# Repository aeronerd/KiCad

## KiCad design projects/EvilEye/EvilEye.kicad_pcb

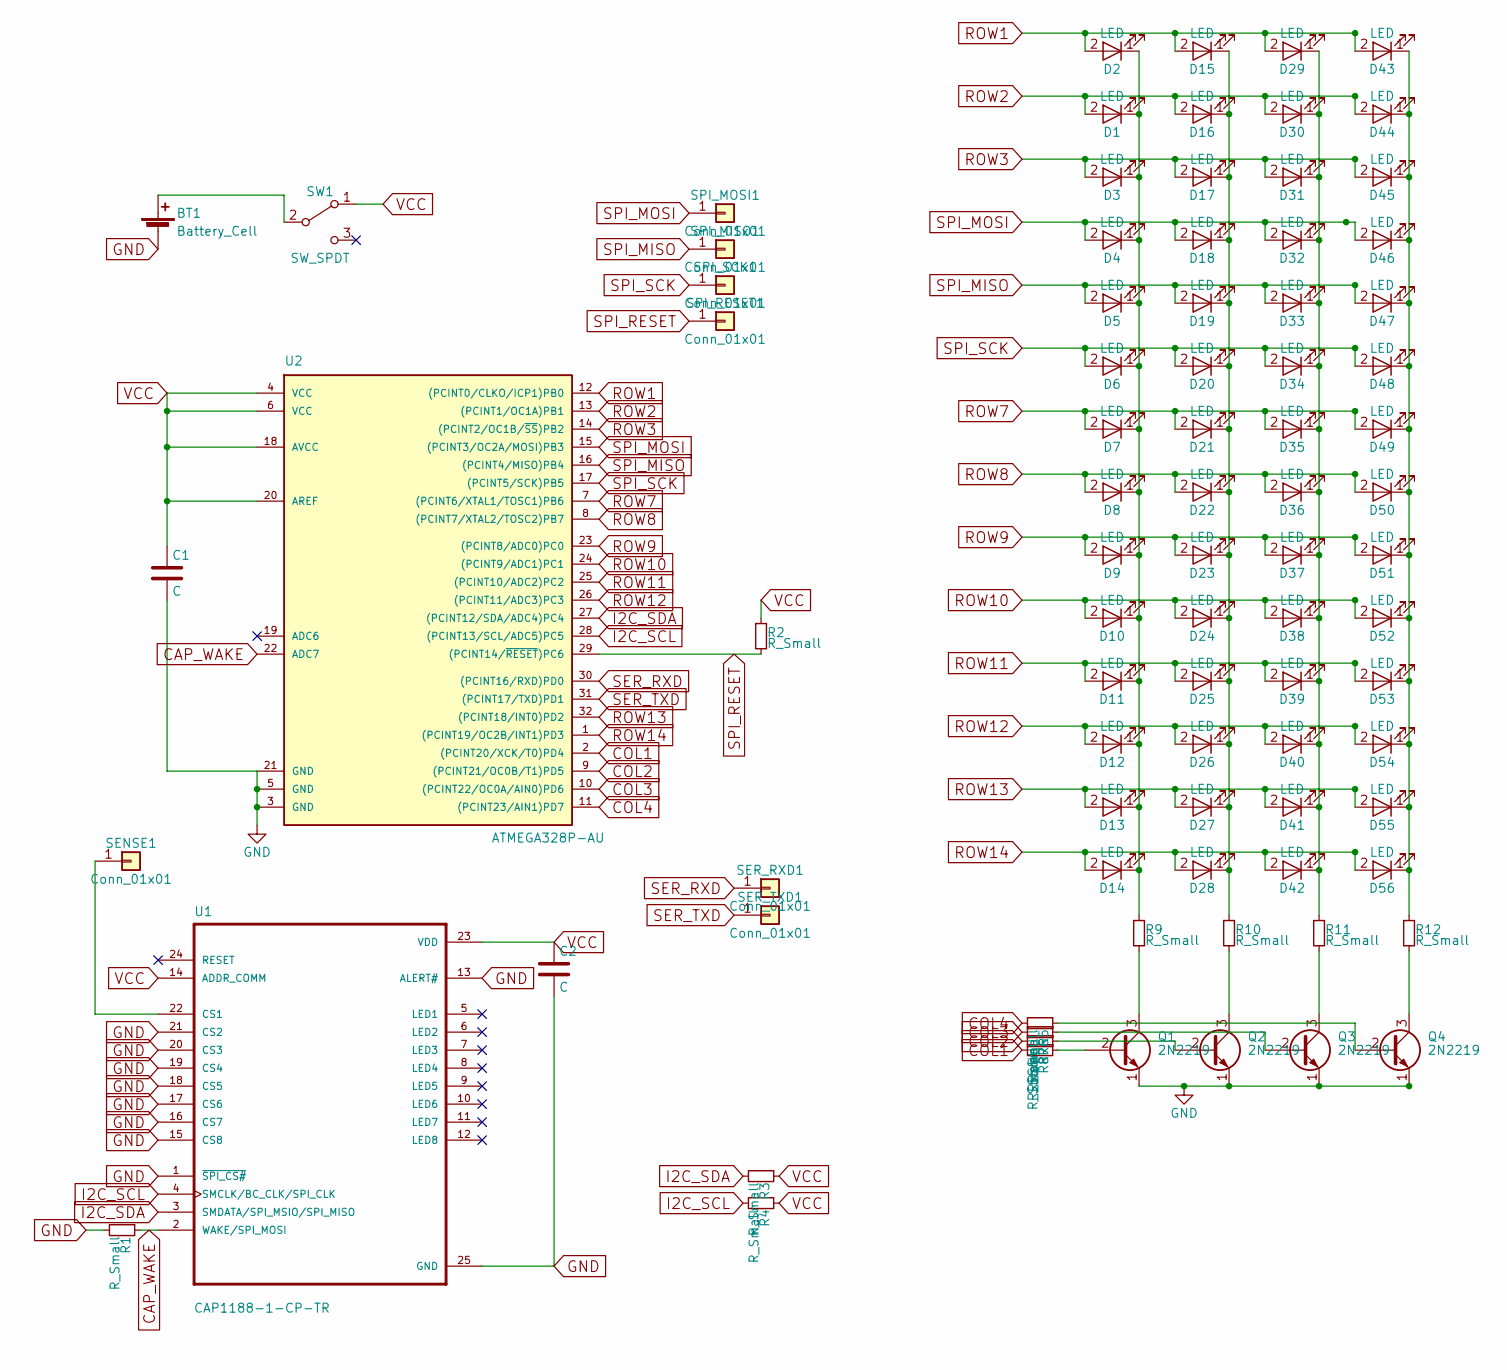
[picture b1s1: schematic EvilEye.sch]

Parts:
BT1: Battery_Cell; 2032-CoinCell-top-bottom
C1, C2: C; C_0603
D1, D2, D3, D4, D5, D6, D7, D8, D9, D10, D11, D12, D13, D14, D15, D16, D17, D18, D19, D20, D21, D22, D23, D24, D25, D26, D27, D28, D29, D30, D31, D32, D33, D34, D35, D36, D37, D38, D39, D40, D41, D42, D43, D44, D45, D46, D47, D48, D49, D50, D51, D52, D53, D54, D55, D56: LED; LED_1206
Q1, Q2, Q3, Q4: 2N2219; SOT23
R1, R2, R3, R4, R5, R6, R7, R8, R9, R10, R11, R12: R_Small; R_0603
SENSE1: Conn_01x01; Measurement_Point_Square-SMD-Pad_Small
SER_RXD1: Conn_01x01; Measurement_Point_Square-SMD-Pad_Small
SER_TXD1: Conn_01x01; Measurement_Point_Square-SMD-Pad_Small
SPI_MISO1: Conn_01x01; Measurement_Point_Square-SMD-Pad_Small
SPI_MOSI1: Conn_01x01; Measurement_Point_Square-SMD-Pad_Small
SPI_RESET1: Conn_01x01; Measurement_Point_Square-SMD-Pad_Small
SPI_SCK1: Conn_01x01; Measurement_Point_Square-SMD-Pad_Small
SW1: SW_SPDT; SW_SPDT_SMD
U1: CAP1188-1-CP-TR; QFN50P400X400X90-25N
U2: ATMEGA328P-AU; TQFP-32_7x7mm_Pitch0.8mm

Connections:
CAP_WAKE: R1.1, U1.2 (WAKE/SPI_MOSI), U2.22 (ADC7)
COL1: R8.2, U2.2 ((PCINT20/XCK/T0)PD4)
COL2: R7.2, U2.9 ((PCINT21/OC0B/T1)PD5)
COL3: R6.2, U2.10 ((PCINT22/OC0A/AIN0)PD6)
COL4: R5.2, U2.11 ((PCINT23/AIN1)PD7)
GND: BT1.2 (-), C1.2, C2.2, Q1.1 (E), Q2.1 (E), Q3.1 (E), Q4.1 (E), R1.2, U1.1 (~SPI_CS#~), U1.13 (ALERT#), U1.15 (CS8), U1.16 (CS7), U1.17 (CS6), U1.18 (CS5), U1.19 (CS4), U1.20 (CS3), U1.21 (CS2), U1.25 (GND), U2.3 (GND), U2.5 (GND), U2.21 (GND)
I2C_SCL: R4.2, U1.4 (SMCLK/BC_CLK/SPI_CLK), U2.28 ((PCINT13/SCL/ADC5)PC5)
I2C_SDA: R3.2, U1.3 (SMDATA/SPI_MSIO/SPI_MISO), U2.27 ((PCINT12/SDA/ADC4)PC4)
unnamed: BT1.1 (+), SW1.2 (B)
unnamed: D1.1 (K), D2.1 (K), D3.1 (K), D4.1 (K), D5.1 (K), D6.1 (K), D7.1 (K), D8.1 (K), D9.1 (K), D10.1 (K), D11.1 (K), D12.1 (K), D13.1 (K), D14.1 (K), R9.1
unnamed: D15.1 (K), D16.1 (K), D17.1 (K), D18.1 (K), D19.1 (K), D20.1 (K), D21.1 (K), D22.1 (K), D23.1 (K), D24.1 (K), D25.1 (K), D26.1 (K), D27.1 (K), D28.1 (K), R10.1
unnamed: D29.1 (K), D30.1 (K), D31.1 (K), D32.1 (K), D33.1 (K), D34.1 (K), D35.1 (K), D36.1 (K), D37.1 (K), D38.1 (K), D39.1 (K), D40.1 (K), D41.1 (K), D42.1 (K), R11.1
unnamed: D43.1 (K), D44.1 (K), D45.1 (K), D46.1 (K), D47.1 (K), D48.1 (K), D49.1 (K), D50.1 (K), D51.1 (K), D52.1 (K), D53.1 (K), D54.1 (K), D55.1 (K), D56.1 (K), R12.1
unnamed: Q1.2 (B), R8.1
unnamed: Q1.3 (C), R9.2
unnamed: Q2.2 (B), R7.1
unnamed: Q2.3 (C), R10.2
unnamed: Q3.2 (B), R6.1
unnamed: Q3.3 (C), R11.2
unnamed: Q4.2 (B), R5.1
unnamed: Q4.3 (C), R12.2
unnamed: SENSE1.1, U1.22 (CS1)
ROW1: D2.2 (A), D15.2 (A), D29.2 (A), D43.2 (A), U2.12 ((PCINT0/CLKO/ICP1)PB0)
ROW2: D1.2 (A), D16.2 (A), D30.2 (A), D44.2 (A), U2.13 ((PCINT1/OC1A)PB1)
ROW3: D3.2 (A), D17.2 (A), D31.2 (A), D45.2 (A), U2.14 ((PCINT2/OC1B/~SS~)PB2)
ROW7: D7.2 (A), D21.2 (A), D35.2 (A), D49.2 (A), U2.7 ((PCINT6/XTAL1/TOSC1)PB6)
ROW8: D8.2 (A), D22.2 (A), D36.2 (A), D50.2 (A), U2.8 ((PCINT7/XTAL2/TOSC2)PB7)
ROW9: D9.2 (A), D23.2 (A), D37.2 (A), D51.2 (A), U2.23 ((PCINT8/ADC0)PC0)
ROW10: D10.2 (A), D24.2 (A), D38.2 (A), D52.2 (A), U2.24 ((PCINT9/ADC1)PC1)
ROW11: D11.2 (A), D25.2 (A), D39.2 (A), D53.2 (A), U2.25 ((PCINT10/ADC2)PC2)
ROW12: D12.2 (A), D26.2 (A), D40.2 (A), D54.2 (A), U2.26 ((PCINT11/ADC3)PC3)
ROW13: D13.2 (A), D27.2 (A), D41.2 (A), D55.2 (A), U2.32 ((PCINT18/INT0)PD2)
ROW14: D14.2 (A), D28.2 (A), D42.2 (A), D56.2 (A), U2.1 ((PCINT19/OC2B/INT1)PD3)
SER_RXD: SER_RXD1.1, U2.30 ((PCINT16/RXD)PD0)
SER_TXD: SER_TXD1.1, U2.31 ((PCINT17/TXD)PD1)
SPI_MISO: D5.2 (A), D19.2 (A), D33.2 (A), D47.2 (A), SPI_MISO1.1, U2.16 ((PCINT4/MISO)PB4)
SPI_MOSI: D4.2 (A), D18.2 (A), D32.2 (A), D46.2 (A), SPI_MOSI1.1, U2.15 ((PCINT3/OC2A/MOSI)PB3)
SPI_RESET: R2.2, SPI_RESET1.1, U2.29 ((PCINT14/~RESET~)PC6)
SPI_SCK: D6.2 (A), D20.2 (A), D34.2 (A), D48.2 (A), SPI_SCK1.1, U2.17 ((PCINT5/SCK)PB5)
VCC: C1.1, C2.1, R2.1, R3.1, R4.1, SW1.1 (A), U1.14 (ADDR_COMM), U1.23 (VDD), U2.4 (VCC), U2.6 (VCC), U2.18 (AVCC), U2.20 (AREF)

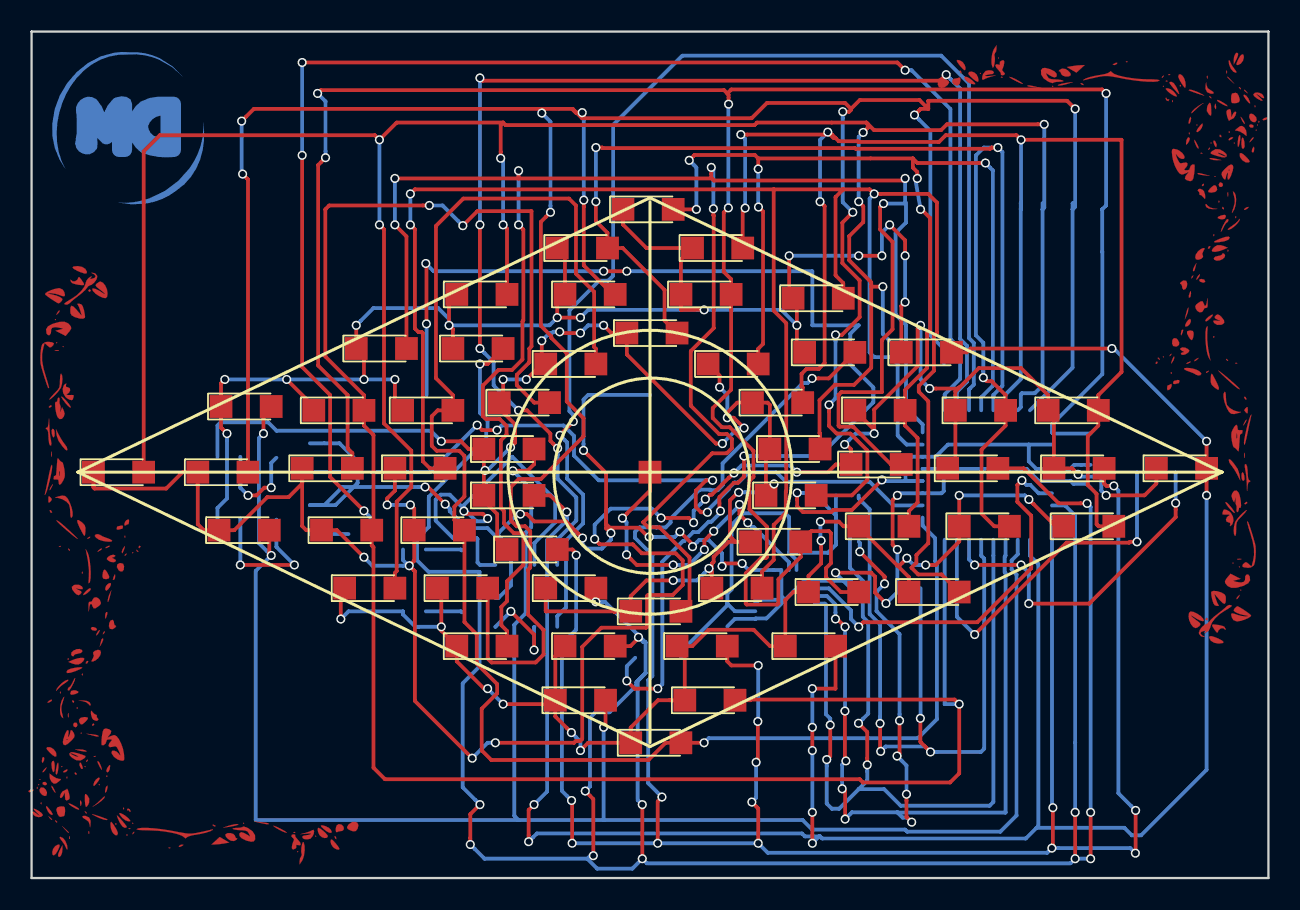
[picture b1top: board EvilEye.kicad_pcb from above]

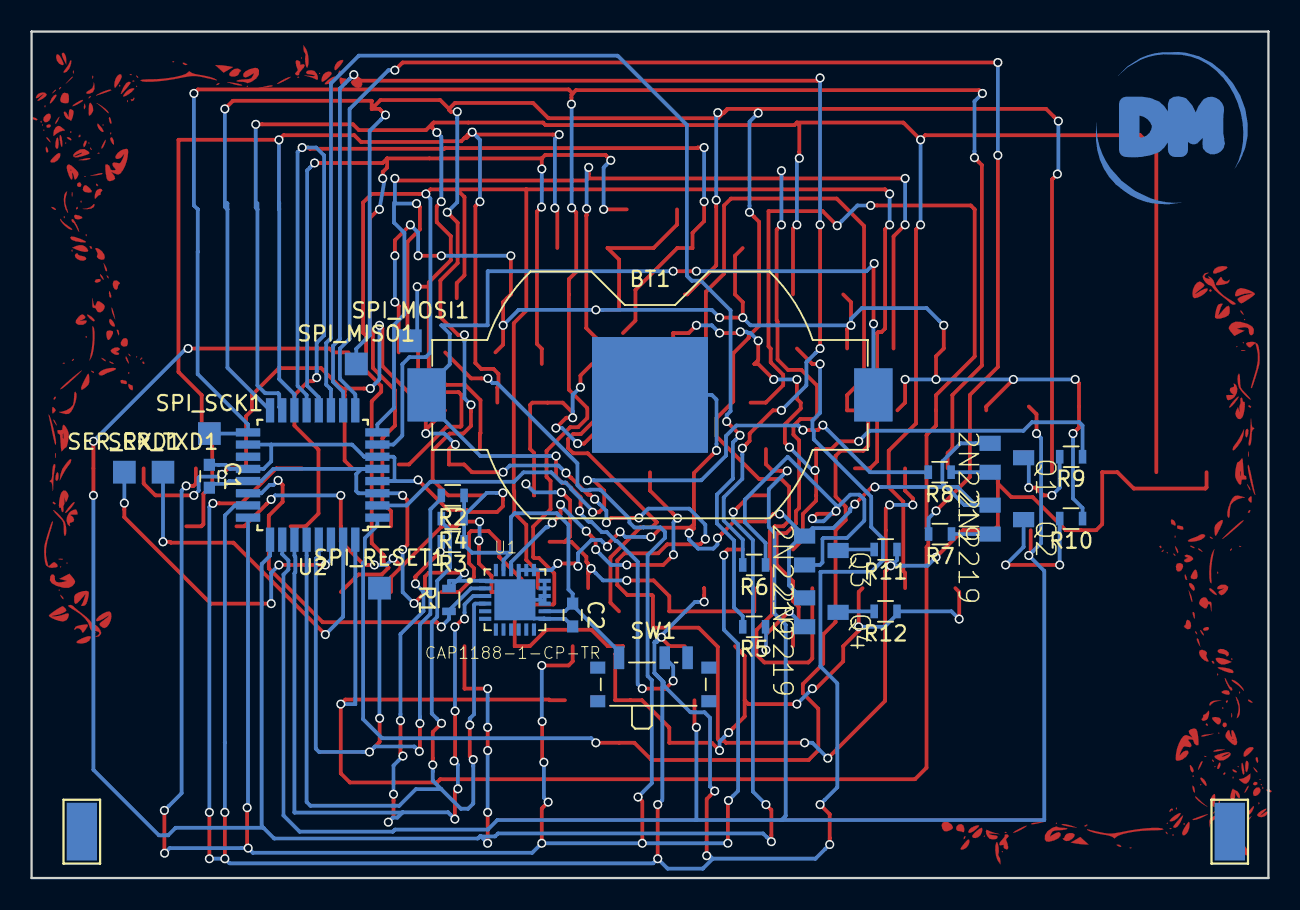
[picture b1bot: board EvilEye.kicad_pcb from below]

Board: 2 copper layers, 81.3 x 55.6 mm, 86 parts (29 on the bottom side), 40 nets.

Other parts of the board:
svg2mod: G***; logo_dm_10x10mm

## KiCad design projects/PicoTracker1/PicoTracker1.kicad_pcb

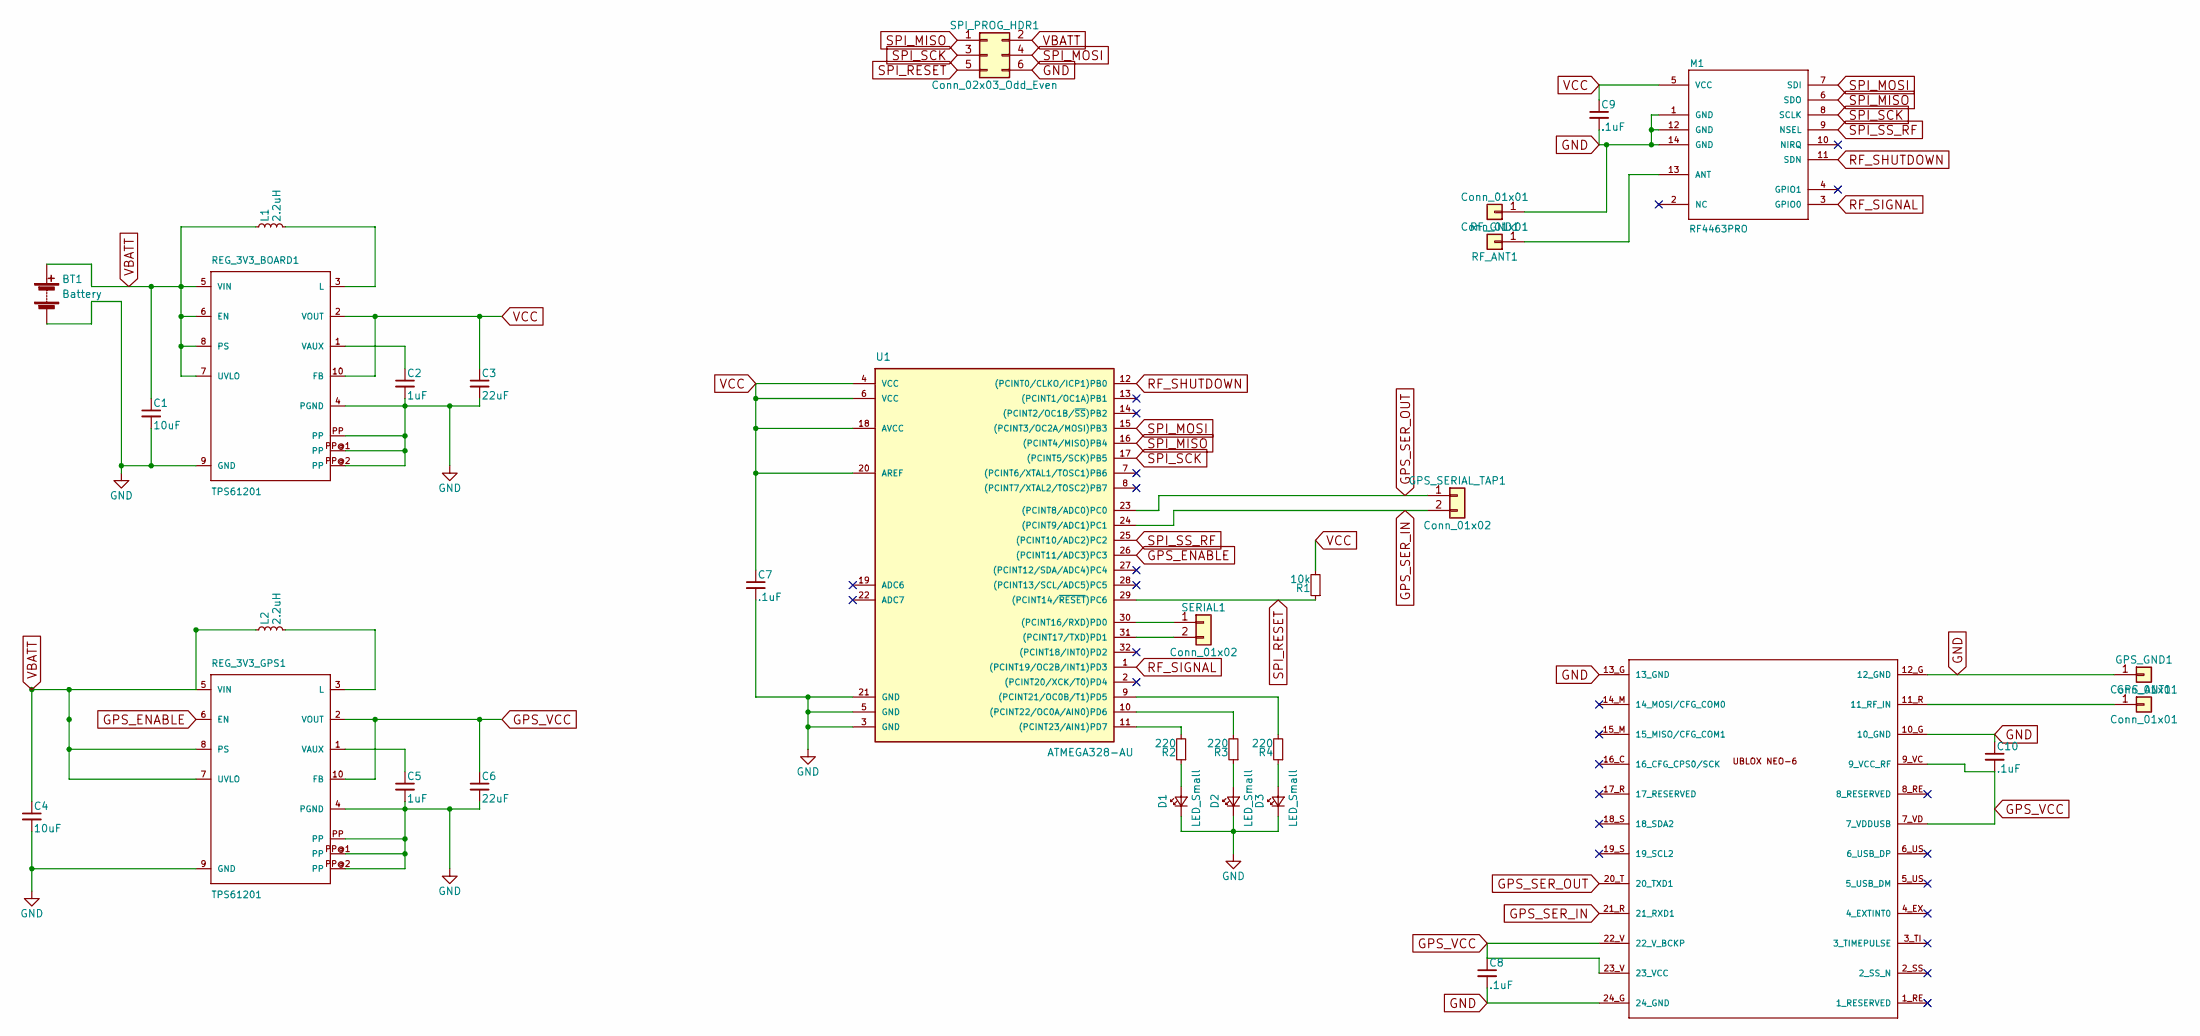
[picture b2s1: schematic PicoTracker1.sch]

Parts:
BT1: Battery; Pin_Header_Straight_1x02_Pitch2.54mm
C1, C4: 10uF; C_0603_HandSoldering
C2, C5: 1uF; C_0603_HandSoldering
C3, C6: 22uF; C_0603_HandSoldering
C7, C8, C9, C10: .1uF; C_0603_HandSoldering
D1, D2, D3: LED_Small; LED_0603_HandSoldering
GPS_ANT1: Conn_01x01; Measurement_Point_Square-SMD-Pad_Big
GPS_GND1: Conn_01x01; Measurement_Point_Square-SMD-Pad_Big
GPS_SERIAL_TAP1: Conn_01x02; Pin_Header_Straight_1x02_Pitch2.54mm
L1, L2: 2.2uH; L_0603_HandSoldering
M1: RF4463PRO; RF4436PRO-STD_BOARD
M2: UBLOX_NEO-6
R1: 10k; R_0603_HandSoldering
R2, R3, R4: 220; R_0603_HandSoldering
REG_3V3_BOARD1, REG_3V3_GPS1: TPS61201; texas-S-PDSO-N10
RF_ANT1: Conn_01x01; Measurement_Point_Square-SMD-Pad_Big
RF_GND1: Conn_01x01; Measurement_Point_Square-SMD-Pad_Big
SERIAL1: Conn_01x02; Pin_Header_Straight_1x02_Pitch2.54mm
SPI_PROG_HDR1: Conn_02x03_Odd_Even; Pin_Header_Straight_2x03_Pitch2.54mm
U1: ATMEGA328-AU; TQFP-32_7x7mm_Pitch0.8mm

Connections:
GND: BT1.2 (-), C1.2, C2.2, C3.2, C4.2, C5.2, C6.2, C7.2, C8.2, C9.2, C10.1, D1.1 (K), D2.1 (K), D3.1 (K), GPS_GND1.1, M1.1 (GND), M1.12 (GND), M1.14 (GND), M2.10_G (10_GND), M2.12_G (12_GND), M2.13_G (13_GND), M2.24_G (24_GND), REG_3V3_BOARD1.4 (PGND), REG_3V3_BOARD1.9 (GND), REG_3V3_BOARD1.PP, REG_3V3_BOARD1.PP@1 (PP), REG_3V3_BOARD1.PP@2 (PP), REG_3V3_GPS1.4 (PGND), REG_3V3_GPS1.9 (GND), REG_3V3_GPS1.PP, REG_3V3_GPS1.PP@1 (PP), REG_3V3_GPS1.PP@2 (PP), RF_GND1.1, SPI_PROG_HDR1.6, U1.3 (GND), U1.5 (GND), U1.21 (GND)
GPS_ENABLE: REG_3V3_GPS1.6 (EN), U1.26 ((PCINT11/ADC3)PC3)
GPS_SER_IN: GPS_SERIAL_TAP1.2, M2.21_R (21_RXD1), U1.24 ((PCINT9/ADC1)PC1)
GPS_SER_OUT: GPS_SERIAL_TAP1.1, M2.20_T (20_TXD1), U1.23 ((PCINT8/ADC0)PC0)
GPS_VCC: C6.1, C8.1, C10.2, M2.7_VD (7_VDDUSB), M2.9_VC (9_VCC_RF), M2.22_V (22_V_BCKP), M2.23_V (23_VCC), REG_3V3_GPS1.2 (VOUT), REG_3V3_GPS1.10 (FB)
unnamed: C2.1, REG_3V3_BOARD1.1 (VAUX)
unnamed: C5.1, REG_3V3_GPS1.1 (VAUX)
unnamed: D1.2 (A), R2.1
unnamed: D2.2 (A), R3.1
unnamed: D3.2 (A), R4.1
unnamed: GPS_ANT1.1, M2.11_R (11_RF_IN)
unnamed: L1.2, REG_3V3_BOARD1.3 (L)
unnamed: L2.2, REG_3V3_GPS1.3 (L)
unnamed: M1.13 (ANT), RF_ANT1.1
unnamed: R2.2, U1.11 ((PCINT23/AIN1)PD7)
unnamed: R3.2, U1.10 ((PCINT22/OC0A/AIN0)PD6)
unnamed: R4.2, U1.9 ((PCINT21/OC0B/T1)PD5)
unnamed: SERIAL1.1, U1.30 ((PCINT16/RXD)PD0)
unnamed: SERIAL1.2, U1.31 ((PCINT17/TXD)PD1)
RF_SHUTDOWN: M1.11 (SDN), U1.12 ((PCINT0/CLKO/ICP1)PB0)
RF_SIGNAL: M1.3 (GPIO0), U1.1 ((PCINT19/OC2B/INT1)PD3)
SPI_MISO: M1.6 (SDO), SPI_PROG_HDR1.1, U1.16 ((PCINT4/MISO)PB4)
SPI_MOSI: M1.7 (SDI), SPI_PROG_HDR1.4, U1.15 ((PCINT3/OC2A/MOSI)PB3)
SPI_RESET: R1.1, SPI_PROG_HDR1.5, U1.29 ((PCINT14/~RESET~)PC6)
SPI_SCK: M1.8 (SCLK), SPI_PROG_HDR1.3, U1.17 ((PCINT5/SCK)PB5)
SPI_SS_RF: M1.9 (NSEL), U1.25 ((PCINT10/ADC2)PC2)
VBATT: BT1.1 (+), C1.1, C4.1, L1.1, L2.1, REG_3V3_BOARD1.5 (VIN), REG_3V3_BOARD1.6 (EN), REG_3V3_BOARD1.7 (UVLO), REG_3V3_BOARD1.8 (PS), REG_3V3_GPS1.5 (VIN), REG_3V3_GPS1.7 (UVLO), REG_3V3_GPS1.8 (PS), SPI_PROG_HDR1.2
VCC: C3.1, C7.1, C9.1, M1.5 (VCC), R1.2, REG_3V3_BOARD1.2 (VOUT), REG_3V3_BOARD1.10 (FB), U1.4 (VCC), U1.6 (VCC), U1.18 (AVCC), U1.20 (AREF)

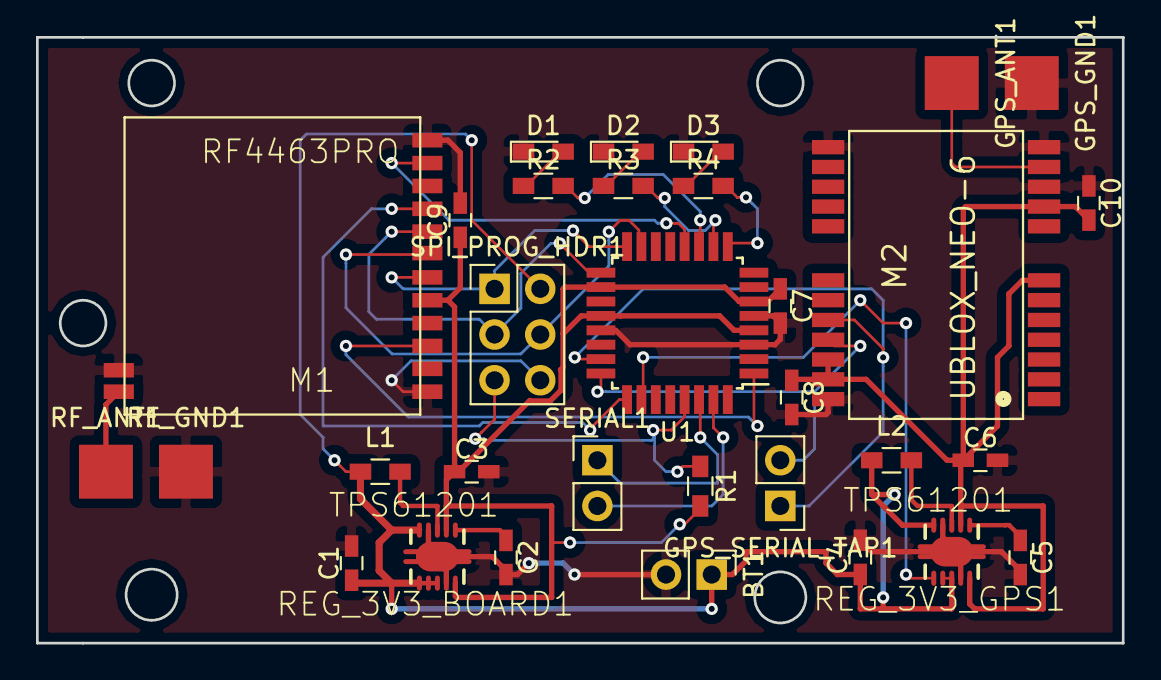
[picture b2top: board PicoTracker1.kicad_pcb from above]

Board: 2 copper layers, 60.3 x 33.7 mm, 32 parts (0 on the bottom side), 28 nets.

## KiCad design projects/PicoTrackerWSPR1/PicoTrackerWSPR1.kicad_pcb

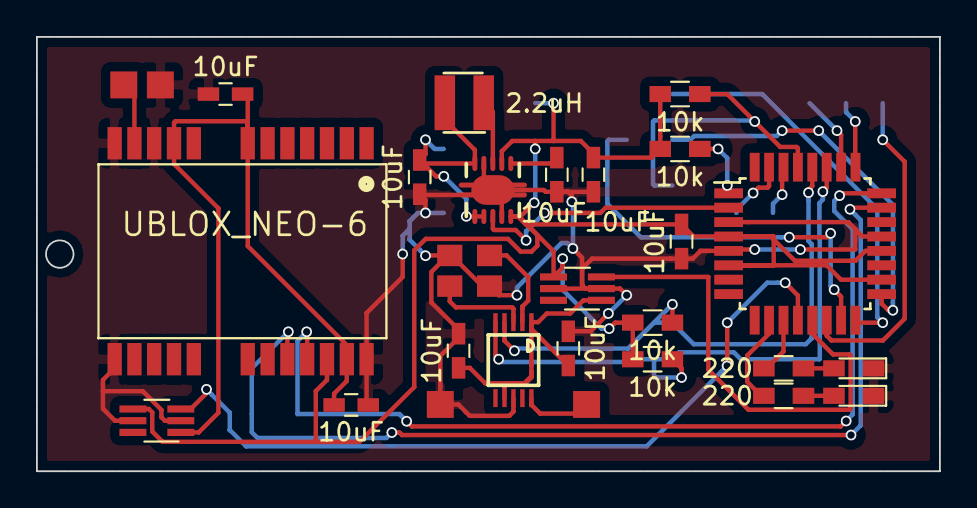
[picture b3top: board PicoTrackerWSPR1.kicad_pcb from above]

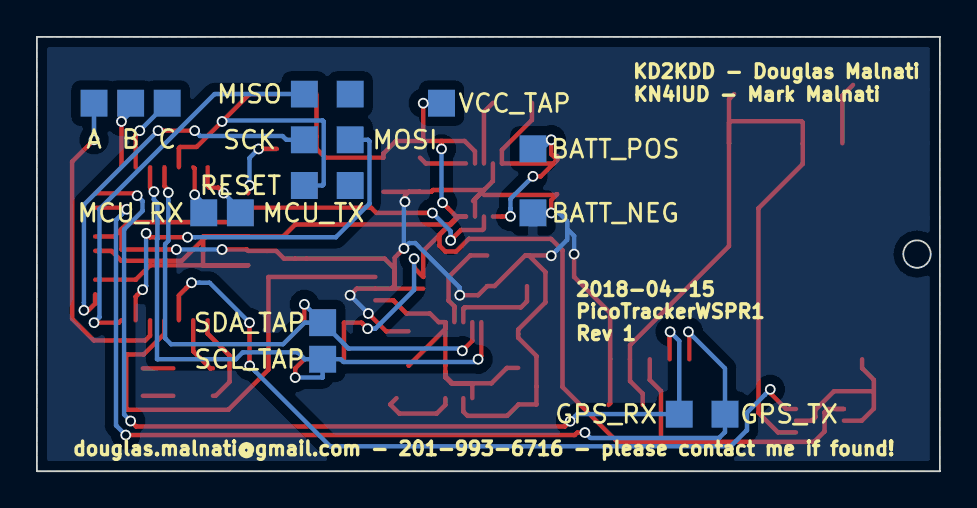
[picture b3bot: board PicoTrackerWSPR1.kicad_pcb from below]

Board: 2 copper layers, 50.2 x 24.1 mm, 46 parts (18 on the bottom side), 32 nets.

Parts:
C1, C2, C3, C4, C5, C6, C7, C8: 10uF; C_0603_HandSoldering
CONN1: BATT_POS; Measurement_Point_Square-SMD-Pad_Small
CONN2: BATT_NEG; Measurement_Point_Square-SMD-Pad_Small
CONN3: MCU_RX; Measurement_Point_Square-SMD-Pad_Small
CONN4: MCU_TX; Measurement_Point_Square-SMD-Pad_Small
CONN5: GPS_RF_GND; Measurement_Point_Square-SMD-Pad_Small
CONN6: GPS_RF_IN; Measurement_Point_Square-SMD-Pad_Small
CONN7: GPS_TX; Measurement_Point_Square-SMD-Pad_Small
CONN8: GPS_RX; Measurement_Point_Square-SMD-Pad_Small
CONN9: WSPR_RF_GND; Measurement_Point_Square-SMD-Pad_Small
CONN10: WSPR_RF_OUT; Measurement_Point_Square-SMD-Pad_Small
CONN11: A; Measurement_Point_Square-SMD-Pad_Small
CONN12: B; Measurement_Point_Square-SMD-Pad_Small
CONN13: C; Measurement_Point_Square-SMD-Pad_Small
CONN14: SCL_TAP; Measurement_Point_Square-SMD-Pad_Small
CONN15: SDA_TAP; Measurement_Point_Square-SMD-Pad_Small
CONN16: MISO; Measurement_Point_Square-SMD-Pad_Small
CONN17: SCK; Measurement_Point_Square-SMD-Pad_Small
CONN18: RESET; Measurement_Point_Square-SMD-Pad_Small
CONN19: VBATT; Measurement_Point_Square-SMD-Pad_Small
CONN20: MOSI; Measurement_Point_Square-SMD-Pad_Small
CONN21: GND; Measurement_Point_Square-SMD-Pad_Small
CONN22: VCC_TAP; Measurement_Point_Square-SMD-Pad_Small
D1, D2: LED_Small; LED_0603_HandSoldering
L1: 2.2uH; coilcraft-LPS3015-222
M1, M2: SIP32431DR3-T1GE3; SOT-363_SC-70-6_Handsoldering
M3: UBLOX_NEO-6
M4: SI5351A; MSOP10
R1, R2: 220; R_0603_HandSoldering
R3, R4, R5, R6: 10k; R_0603_HandSoldering
REG_3V3_BOARD1: TPS61201; texas-S-PDSO-N10
U1: ATMEGA328-AU; TQFP-32_7x7mm_Pitch0.8mm
Y1: CRYSTAL_ABM8G; ABM8G-25.000MHZ-B4Y-T

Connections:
GND: C1.2, C2.2, C3.2, C4.2, C5.2, C6.2, C7.1, C8.1, CONN2.1, CONN5.1, CONN9.1, D1.1, D2.1, M1.2, M1.5, M2.2, M2.5, M3.10_G, M3.12_G, M3.13_G, M3.24_G, M4.8, REG_3V3_BOARD1.4, REG_3V3_BOARD1.9, REG_3V3_BOARD1.PP, REG_3V3_BOARD1.PP@1, REG_3V3_BOARD1.PP@2, U1.3, U1.5, U1.21, Y1.2, Y1.4
GPS_ENABLE: M1.3, U1.12
GPS_RF_IN: CONN6.1, M3.11_R
GPS_SER_IN: CONN8.1, M3.21_R, U1.24
GPS_SER_OUT: CONN7.1, M3.20_T, U1.23
GPS_VCC: C5.1, C7.2, M1.1, M3.7_VD, M3.9_VC, M3.23_V
LED_1: R1.2, U1.10
LED_2: R2.2, U1.11
unnamed: C3.1, REG_3V3_BOARD1.1
unnamed: D1.2, R1.1
unnamed: D2.2, R2.1
unnamed: L1.2, REG_3V3_BOARD1.3
unnamed: M4.2, Y1.1
unnamed: M4.3, Y1.3
REG_PS_CTL: REG_3V3_BOARD1.8, U1.2
RESET: R3.2, U1.1
SCL: CONN15.1, M4.4, R5.2, U1.28
SDA: CONN14.1, M4.5, R4.2, U1.27
SER_RXD: CONN3.1, U1.30
SER_TXD: CONN4.1, U1.31
SIG_A: CONN11.1, U1.14
SIG_B: CONN12.1, U1.25
SIG_C: CONN13.1, U1.26
SPI_MISO: CONN16.1, U1.16
SPI_MOSI: CONN20.1, U1.15
SPI_RESET: CONN18.1, R6.2, U1.29
SPI_SCK: CONN17.1, U1.17
VBATT: C2.1, CONN1.1, L1.1, REG_3V3_BOARD1.5, REG_3V3_BOARD1.6, REG_3V3_BOARD1.7
VCC: C1.1, C4.1, CONN22.1, M1.4, M2.4, M3.22_V, R3.1, R4.1, R5.1, R6.1, REG_3V3_BOARD1.2, REG_3V3_BOARD1.10, U1.4, U1.6, U1.18, U1.20
WSPR_ENABLE: M2.3, U1.13
WSPR_RF_OUT: CONN10.1, M4.10
WSPR_VCC: C6.1, C8.2, M2.1, M4.1, M4.7

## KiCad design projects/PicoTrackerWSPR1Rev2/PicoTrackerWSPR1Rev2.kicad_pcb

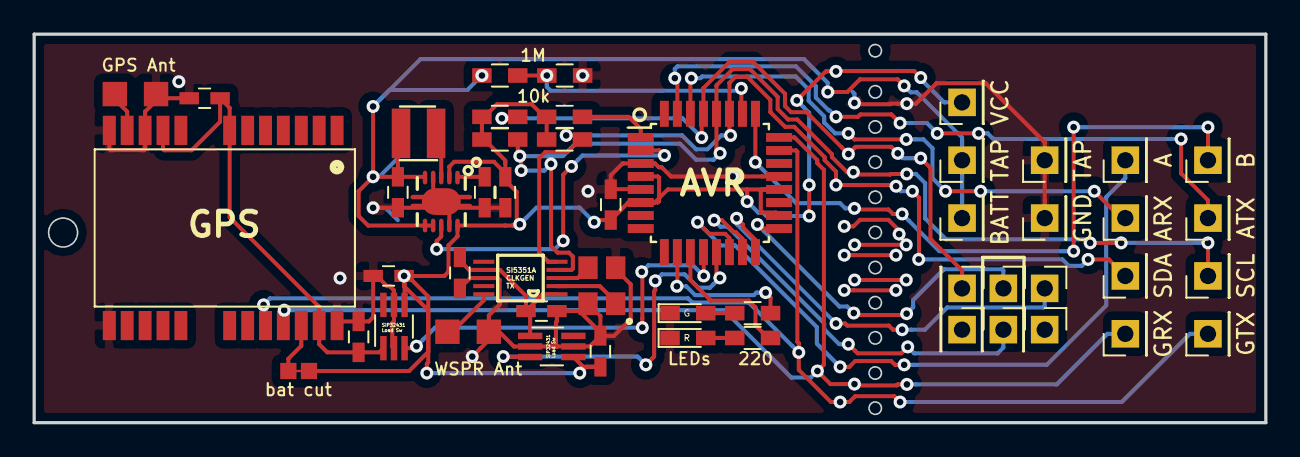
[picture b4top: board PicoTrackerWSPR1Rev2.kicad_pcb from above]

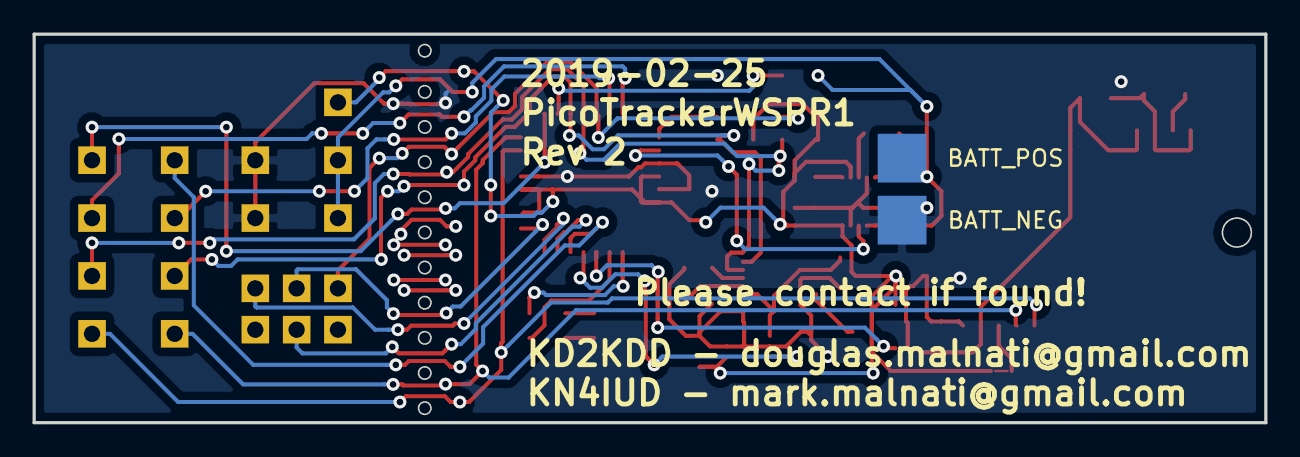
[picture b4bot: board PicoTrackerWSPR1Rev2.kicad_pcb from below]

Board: 2 copper layers, 75.7 x 23.9 mm, 54 parts (2 on the bottom side), 33 nets.

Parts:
C1, C2, C3, C4, C5, C6, C7, C8, C9, C10: 10uF; C_0603_HandSoldering
CONN1: BATT_NEG; Measurement_Point_Square-SMD-Pad_Big
CONN2: BATT_POS; Measurement_Point_Square-SMD-Pad_Big
CONN3: BATT; Socket_Strip_Straight_1x01_Pitch2.54mm
CONN4: GND; Socket_Strip_Straight_1x01_Pitch2.54mm
CONN5: ARX; Socket_Strip_Straight_1x01_Pitch2.54mm
CONN6: ATX; Socket_Strip_Straight_1x01_Pitch2.54mm
CONN7, CONN25: TAP; Socket_Strip_Straight_1x01_Pitch2.54mm
CONN8: VCC; Socket_Strip_Straight_1x01_Pitch2.54mm
CONN9: SDA; Socket_Strip_Straight_1x01_Pitch2.54mm
CONN10: SCL; Socket_Strip_Straight_1x01_Pitch2.54mm
CONN11: SPI_MISO; Pin_Header_Straight_1x01_Pitch2.54mm
CONN12: SPI_SCK; Pin_Header_Straight_1x01_Pitch2.54mm
CONN13: SPI_RESET; Pin_Header_Straight_1x01_Pitch2.54mm
CONN14: VBATT; Pin_Header_Straight_1x01_Pitch2.54mm
CONN15: SPI_MOSI; Pin_Header_Straight_1x01_Pitch2.54mm
CONN16: GND; Pin_Header_Straight_1x01_Pitch2.54mm
CONN17: GTX; Socket_Strip_Straight_1x01_Pitch2.54mm
CONN18: GRX; Socket_Strip_Straight_1x01_Pitch2.54mm
CONN19: A; Socket_Strip_Straight_1x01_Pitch2.54mm
CONN20: B; Socket_Strip_Straight_1x01_Pitch2.54mm
CONN21: GPS_RF_GND; Measurement_Point_Square-SMD-Pad_Small
CONN22: GPS_RF_IN; Measurement_Point_Square-SMD-Pad_Small
CONN23: WSPR_RF_GND; Measurement_Point_Square-SMD-Pad_Small
CONN24: WSPR_RF_OUT; Measurement_Point_Square-SMD-Pad_Small
D1, D2: LED_Small; LED_0603_HandSoldering
J1: Conn_01x02; CUT_TRACE
L1: 2.2uH; coilcraft-LPS3015-222
M1, M2: SIP32431DR3-T1GE3; SOT-363_SC-70-6_Handsoldering
M3: UBLOX_NEO-6
M4: SI5351A
R1, R2: 220; R_0603_HandSoldering
R3, R4, R5, R6: 10k; R_0603_HandSoldering
R7, R8: 1M; R_0603_HandSoldering
REG_3V3_BOARD1: TPS61201; texas-S-PDSO-N10
U1: ATMEGA328P-AU; TQFP-32_7x7mm_Pitch0.8mm
Y1: CRYSTAL_ABM8G; ABM8G-25.000MHZ-B4Y-T

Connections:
GND: C1.2, C2.2, C3.2, C4.2, C5.2, C6.1, C7.2, C8.1, C9.1, C10.1, CONN1.1, CONN4.1, CONN21.1, CONN23.1, CONN25.1, D1.1, D2.1, M1.2, M1.5, M2.2, M2.5, M3.10_G, M3.12_G, M3.13_G, M3.24_G, M4.8, R8.1, REG_3V3_BOARD1.4, REG_3V3_BOARD1.9, REG_3V3_BOARD1.PP, REG_3V3_BOARD1.PP@1, REG_3V3_BOARD1.PP@2, U1.3, U1.5, U1.21, Y1.2, Y1.4
GPS_ENABLE: M1.3, U1.12
GPS_RF_IN: CONN22.1, M3.11_R
GPS_SER_IN: CONN18.1, M3.21_R, U1.24
GPS_SER_OUT: CONN17.1, M3.20_T, U1.23
GPS_VCC: C5.1, C9.2, M1.1, M3.7_VD, M3.9_VC, M3.23_V
LED_1: R1.2, U1.10
LED_2: R2.2, U1.11
unnamed: C3.1, REG_3V3_BOARD1.1
unnamed: D1.2, R1.1
unnamed: D2.2, R2.1
unnamed: J1.2, M3.22_V
unnamed: L1.2, REG_3V3_BOARD1.3
unnamed: M4.2, Y1.1
unnamed: M4.3, Y1.3
REG_PS_CTL: REG_3V3_BOARD1.8, U1.2
RESET: R3.2, U1.1
SCL: CONN10.1, M4.4, R5.2, U1.28
SDA: CONN9.1, M4.5, R4.2, U1.27
SER_RXD: CONN5.1, U1.30
SER_TXD: CONN6.1, U1.31
SIG_A: CONN19.1, U1.14
SIG_B: CONN20.1, U1.25
SPI_MISO: CONN11.1, U1.16
SPI_MOSI: CONN15.1, U1.15
SPI_RESET: CONN13.1, R6.2, U1.29
SPI_SCK: CONN12.1, U1.17
VBATT: C2.1, CONN2.1, CONN3.1, CONN7.1, L1.1, R7.2, REG_3V3_BOARD1.5, REG_3V3_BOARD1.6, REG_3V3_BOARD1.7
VBATT_SENSE: R7.1, R8.2, U1.26
VCC: C1.1, C4.1, C6.2, C8.2, CONN8.1, J1.1, M1.4, M2.4, R3.1, R4.1, R5.1, R6.1, REG_3V3_BOARD1.2, REG_3V3_BOARD1.10, U1.4, U1.6, U1.18, U1.20
WSPR_ENABLE: M2.3, U1.13
WSPR_RF_OUT: CONN24.1, M4.10
WSPR_VCC: C7.1, C10.2, M2.1, M4.1, M4.7

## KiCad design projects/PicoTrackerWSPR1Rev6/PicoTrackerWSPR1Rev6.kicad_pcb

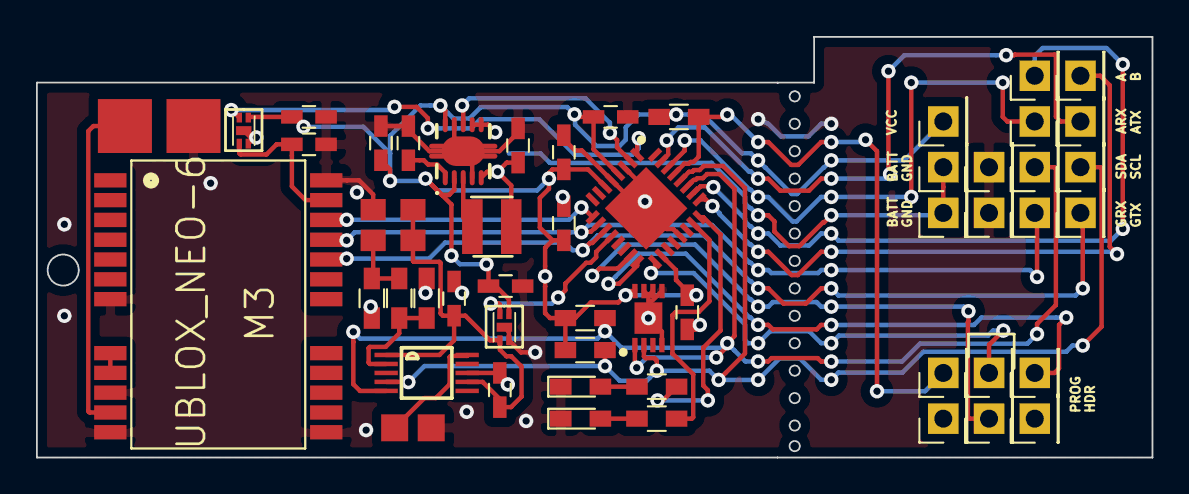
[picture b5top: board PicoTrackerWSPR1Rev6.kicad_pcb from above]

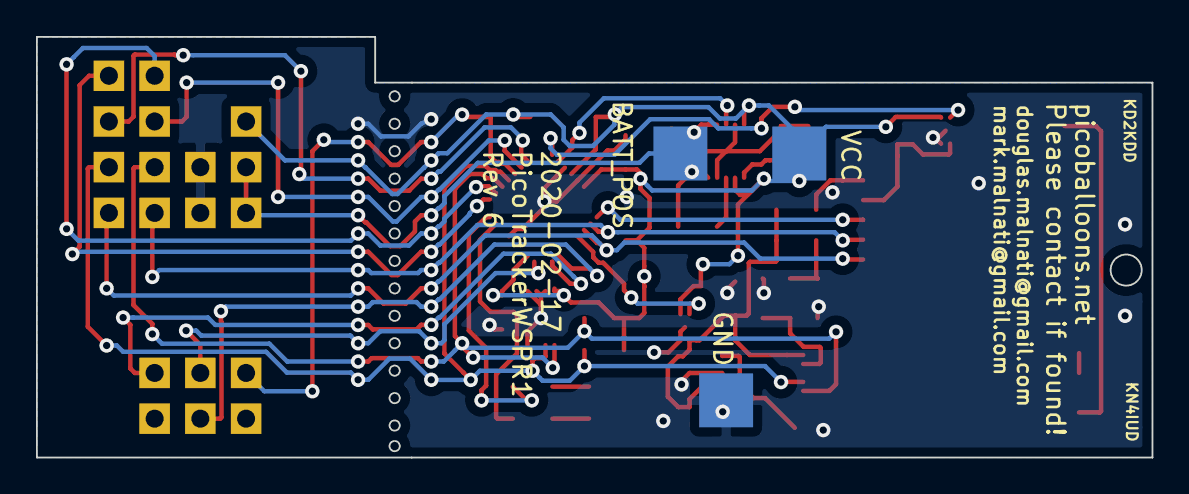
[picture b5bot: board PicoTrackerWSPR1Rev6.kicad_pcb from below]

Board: 2 copper layers, 62.0 x 23.4 mm, 57 parts (3 on the bottom side), 32 nets.

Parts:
C1, C5, C7, C9, C10, C11, C12: .1uF; C_0603_HandSoldering
C2, C4, C6, C8: 22uF; C_0603_HandSoldering
C3: 1uF; C_0603_HandSoldering
CONN1: BATT_NEG; Measurement_Point_Square-SMD-Pad_Big
CONN2: BATT_POS; Measurement_Point_Square-SMD-Pad_Big
CONN3: BATT_INPUT; Socket_Strip_Straight_1x01_Pitch2.54mm
CONN4: GND_INPUT; Socket_Strip_Straight_1x01_Pitch2.54mm
CONN5: MCU_SER_RXD; Socket_Strip_Straight_1x01_Pitch2.54mm
CONN6: MCU_SER_TXD; Socket_Strip_Straight_1x01_Pitch2.54mm
CONN7: BATT_TAP; Socket_Strip_Straight_1x01_Pitch2.54mm
CONN8: VCC_TAP; Socket_Strip_Straight_1x01_Pitch2.54mm
CONN9: SDA_TAP; Socket_Strip_Straight_1x01_Pitch2.54mm
CONN10: SCL_TAP; Socket_Strip_Straight_1x01_Pitch2.54mm
CONN11: SPI_MISO; Pin_Header_Straight_1x01_Pitch2.54mm
CONN12: SPI_SCK; Pin_Header_Straight_1x01_Pitch2.54mm
CONN13: SPI_RESET; Pin_Header_Straight_1x01_Pitch2.54mm
CONN14: VBATT; Pin_Header_Straight_1x01_Pitch2.54mm
CONN15: SPI_MOSI; Pin_Header_Straight_1x01_Pitch2.54mm
CONN16: GND; Pin_Header_Straight_1x01_Pitch2.54mm
CONN17: GPS_SER_OUT; Socket_Strip_Straight_1x01_Pitch2.54mm
CONN18: GPS_SER_IN; Socket_Strip_Straight_1x01_Pitch2.54mm
CONN19: SIG_A; Socket_Strip_Straight_1x01_Pitch2.54mm
CONN20: SIG_B; Socket_Strip_Straight_1x01_Pitch2.54mm
CONN21: GPS_RF_GND; Measurement_Point_Square-SMD-Pad_Big
CONN22: GPS_RF_IN; Measurement_Point_Square-SMD-Pad_Big
CONN23: WSPR_RF_GND; Measurement_Point_Square-SMD-Pad_Small
CONN24: WSPR_RF_OUT; Measurement_Point_Square-SMD-Pad_Small
CONN25: GND_TAP; Socket_Strip_Straight_1x01_Pitch2.54mm
CONN26: VCC_OUTPUT; Measurement_Point_Square-SMD-Pad_Big
D1, D2: LED_Small; LED_0603_HandSoldering
IC1: MCP9808
L1: 2.2uH; coilcraft-LPS3015-222
M3: UBLOX_NEO-6
M4: SI5351A
R1, R2: 220; R_0603_HandSoldering
R3, R4, R6: 10k; R_0603_HandSoldering
R9, R11: 100; R_0603_HandSoldering
R10: 68; R_0603_HandSoldering
REG_3V3_BOARD1: TPS61201; texas-S-PDSO-N10
TCXO2: CRYSTAL_TCXO_3.2mmWidth_2.5mmHeight; CRYSTAL_3.2mmWidth_2.5mmHeight
U1, U2: SIP32431DNP3-T1GE4
U3: ATMEGA328P-MU

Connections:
GND: C1.1, C2.2, C3.2, C4.2, C5.2, C6.2, C7.2, C8.2, C9.1, C10.1, C11.1, C12.2, CONN1.1, CONN4.1, CONN21.1, CONN23.1, CONN25.1, D1.1, D2.1, IC1.4, IC1.5, IC1.6, IC1.7, IC1.9, M3.7_VD, M3.10_G, M3.12_G, M3.13_G, M3.24_G, M4.8, R9.2, R11.2, REG_3V3_BOARD1.4, REG_3V3_BOARD1.9, REG_3V3_BOARD1.PP, REG_3V3_BOARD1.PP@1, REG_3V3_BOARD1.PP@2, TCXO2.2, U1.2, U1.5, U2.2, U2.5, U3.3, U3.5, U3.21, U3.33
GPS_ENABLE: U1.4, U3.1
GPS_RF_IN: CONN22.1, M3.11_R
GPS_SER_IN: CONN18.1, M3.21_R, U3.10
GPS_SER_OUT: CONN17.1, M3.20_T, U3.11
GPS_VCC: C5.1, M3.23_V, U1.1
GPS_V_BCKP: M3.22_V, U3.9
LED_1: R1.2, U3.24
LED_2: R2.2, U3.23
unnamed: C3.1, REG_3V3_BOARD1.1
unnamed: D1.2, R1.1
unnamed: D2.2, R2.1
unnamed: L1.2, REG_3V3_BOARD1.3
unnamed: M3.8_RE, M3.9_VC
unnamed: M4.2, R10.1, R11.1
unnamed: R9.1, R10.2, TCXO2.3
REG_PS_CTL: REG_3V3_BOARD1.8, U3.2
SCL: CONN10.1, IC1.2, M4.4, R6.2, U3.28
SDA: CONN9.1, IC1.1, M4.5, R4.2, U3.27
SER_RXD: CONN5.1, U3.30
SER_TXD: CONN6.1, U3.31
SIG_A: CONN19.1, U3.26
SIG_B: CONN20.1, U3.25
SPI_MISO: CONN11.1, U3.16
SPI_MOSI: CONN15.1, U3.15
SPI_RESET: CONN13.1, R3.2, U3.29
SPI_SCK: CONN12.1, U3.17
VBATT: C2.1, CONN2.1, CONN3.1, CONN7.1, L1.1, REG_3V3_BOARD1.5, REG_3V3_BOARD1.6, REG_3V3_BOARD1.7
VCC: C1.2, C4.1, C6.1, C8.1, C9.2, C11.2, C12.1, CONN8.1, CONN26.1, IC1.8, R3.1, R4.1, R6.1, REG_3V3_BOARD1.2, REG_3V3_BOARD1.10, U1.3, U2.3, U3.4, U3.6, U3.18
WSPR_ENABLE: U2.4, U3.12
WSPR_RF_OUT: CONN24.1, M4.10
WSPR_VCC: C7.1, C10.2, M4.1, M4.7, TCXO2.1, TCXO2.4, U2.1

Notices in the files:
parts and their libraries:
Copyright 2016 Accelerated Designs. All rights reserved.
